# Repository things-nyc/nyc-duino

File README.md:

# nyc-duino

A simple demo board for the TTN NYC Hardware Office Hours!

## Soldering (optional)

Simple introduction to soldering by attaching the DHT11/22 and a 10k thru-hole pullup resistor. Male or female header can also be added to support Arduino shields.

## Arduino

### Installing

```
https://www.arduino.cc/en/Main/Software
```

### Libraries Needed

Sketch -> Include Library -> Manage Libraries

* Adafruit Unified Sensor - by Adafruit
* DHT sensor library - by Adafruit
* TheThingsNetwork - by The Things Network
* CayenneLPP - by The Things Network

## The Things Network

The Things Network is our LoRaWAN network server.

### Create Account

### Create Application

### Add Cayenne Integration

Also choose Cayenne LPP from Payload Formats tab.

### Add Device

Upload DeviceInfo sketch from TheThingsNetwork library to get DevEUI.

## Firmware

Download nycDuino-demo.ino from this repo.

Use the AppEUI and AppKey from TTN dashboard to personalize the Arduino sketch on lines 6 and 7.

Tools -> Board -> Arduino Leonardo

Upload.

## Cayenne

### Create Account

### Add Device

LoRa -> The Things Network -> Cayenne LPP

## Bonus Round

* Don't use delay() to time transmissions
* Use downlink to set onboard LED state
* Lower power by using sleep and idle

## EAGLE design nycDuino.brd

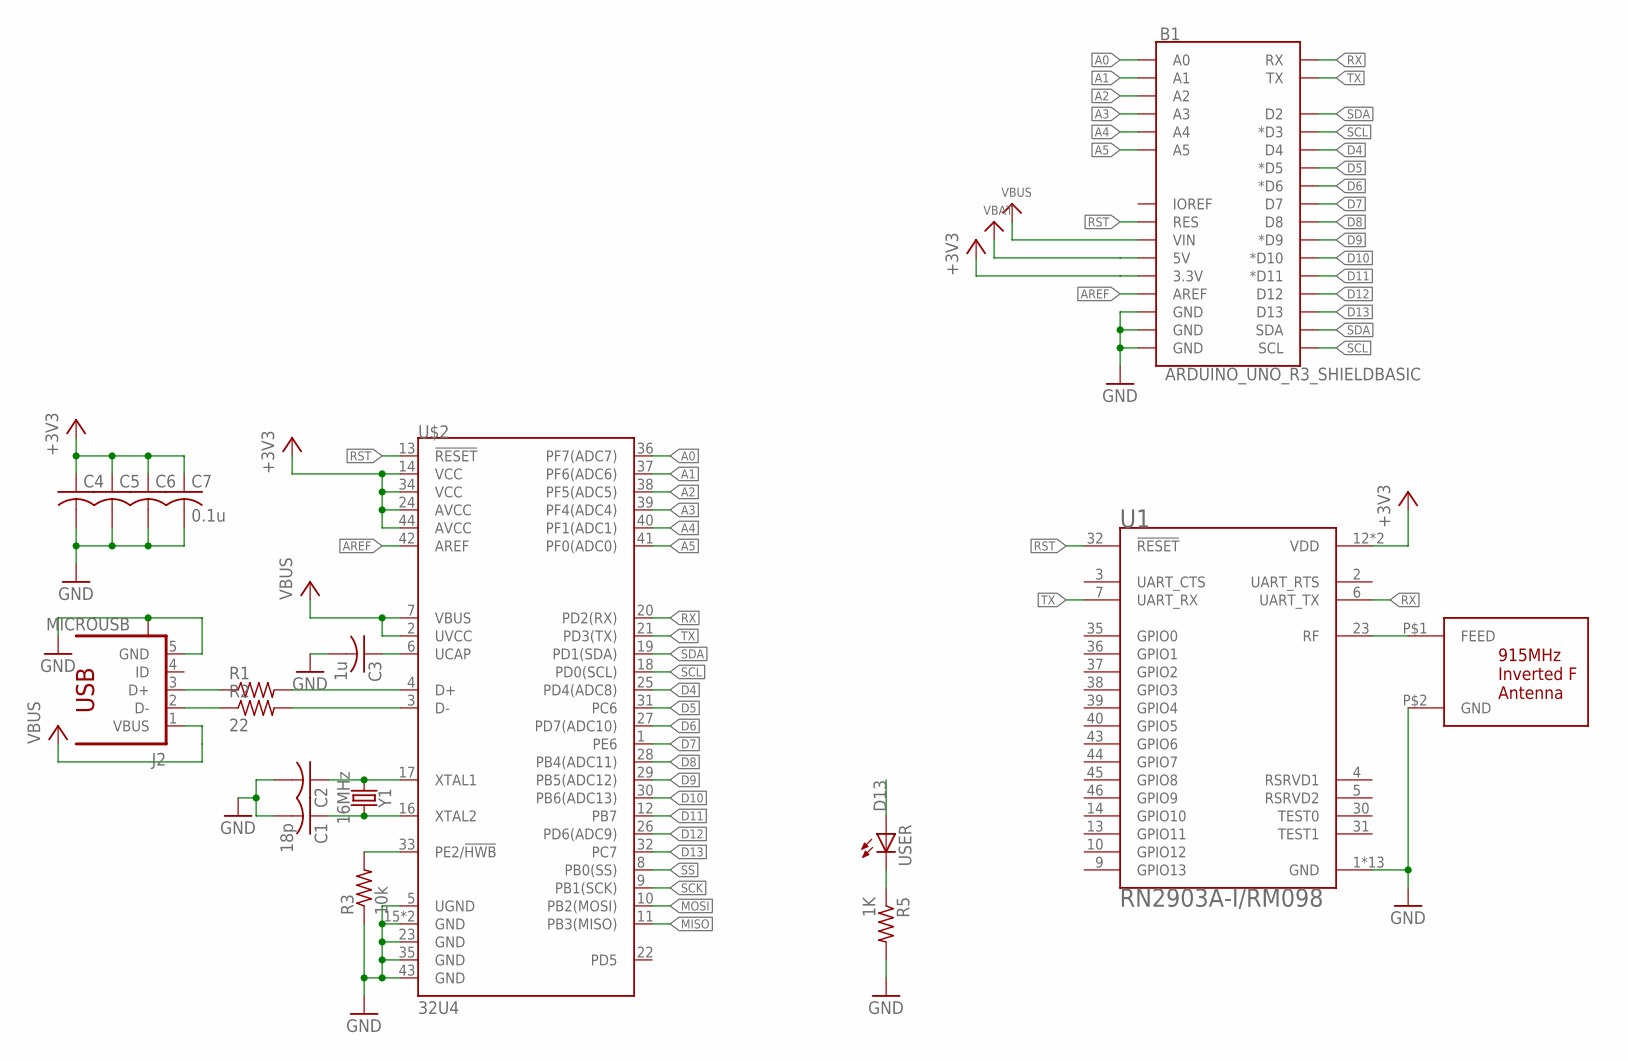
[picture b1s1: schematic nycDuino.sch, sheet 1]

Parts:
B1: ARDUINO_UNO_R3_SHIELDBASIC; UNO_R3_SHIELD
C1: 18p; C0603
C2, C4, C5, C6: C-USC0603; C0603
C3: 1u; C0603
C7: 0.1u; C0603
J2: MICROUSB; 10118192-0001LF
R1: R-US_R0603; R0603
R2: 22; R0603
R3: 10k; R0603
R5: 1K; R0603
U1: RN2903A-I/RM098; XCVR_RN2903A-I/RM098
U$1: 915MHZ; 915MHZ-F-NOMATCH
U$2: 32U4; QFN-44
USER: LEDCHIP-LED0603; CHIP-LED0603
Y1: 16MHz; CRYSTAL-SMD-5X3.2-4PAD

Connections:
+3V3: B1.3.3V, C4.1, C5.1, C6.1, C7.1, U1.12 (VDD), U1.34 (VDD), U$2.14 (VCC), U$2.24 (AVCC), U$2.34 (VCC), U$2.44 (AVCC); also elsewhere on the board
A0: B1.A0, U$2.36 (PF7(ADC7))
A1: B1.A1, U$2.37 (PF6(ADC6))
A2: B1.A2, U$2.38 (PF5(ADC5))
A3: B1.A3, U$2.39 (PF4(ADC4))
A4: B1.A4, U$2.40 (PF1(ADC1))
A5: B1.A5, U$2.41 (PF0(ADC0))
AREF: B1.AREF, U$2.42 (AREF); also elsewhere on the board
D4: B1.D4, U$2.25 (PD4(ADC8)); also elsewhere on the board
D5: B1.D5 (*D5), U$2.31 (PC6)
D6: B1.D6 (*D6), U$2.27 (PD7(ADC10))
D7: B1.D7, U$2.1 (PE6)
D8: B1.D8, U$2.28 (PB4(ADC11))
D9: B1.D9 (*D9), U$2.29 (PB5(ADC12))
D10: B1.D10 (*D10), U$2.30 (PB6(ADC13))
D11: B1.D11 (*D11), U$2.12 (PB7)
D12: B1.D12, U$2.26 (PD6(ADC9))
D13: B1.D13, U$2.32 (PC7), USER.A
GND: B1.GND@0 (GND), B1.GND@1 (GND), B1.GND@2 (GND), C1.2, C2.2, C3.2, C4.2, C5.2, C6.2, C7.2, J2.5 (GND), J2.M1 (S), J2.M2 (S), J2.S1 (S), J2.S2 (S), J2.S3 (S), J2.S4 (S), R3.1, R5.2, U1.1 (GND), U1.8 (GND), U1.11 (GND), U1.20 (GND), U1.21 (GND), U1.22 (GND), U1.24 (GND), U1.26 (GND), U1.27 (GND), U1.28 (GND), U1.33 (GND), U1.41 (GND), U1.47 (GND), U$1.P$2 (GND), U$2.5 (UGND), U$2.15 (GND), U$2.23 (GND), U$2.35 (GND), U$2.43 (GND), U$2.45 (GND); also elsewhere on the board
MISO: U$2.11 (PB3(MISO)); also elsewhere on the board
MOSI: U$2.10 (PB2(MOSI)); also elsewhere on the board
unnamed: U1.23 (RF), U$1.P$1 (FEED)
unnamed: J2.3 (D+), R1.1
unnamed: J2.2 (D-), R2.1
unnamed: R1.2, U$2.4 (D+)
unnamed: R2.2, U$2.3 (D-)
unnamed: C2.1, U$2.17 (XTAL1), Y1.1
unnamed: C1.1, U$2.16 (XTAL2), Y1.3 (2)
unnamed: C3.1, U$2.6 (UCAP)
unnamed: R3.2, U$2.33 (PE2/!HWB)
unnamed: R5.1, USER.C
RST: B1.RES, U1.32 (!RESET), U$2.13 (!RESET); also elsewhere on the board
RX: B1.RX, U1.6 (UART_TX), U$2.20 (PD2(RX))
SCK: U$2.9 (PB1(SCK)); also elsewhere on the board
SCL: B1.D3 (*D3), B1.SCL, U$2.18 (PD0(SCL))
SDA: B1.D2, B1.SDA, U$2.19 (PD1(SDA))
SS: U$2.8 (PB0(SS))
TX: B1.TX, U1.7 (UART_RX), U$2.21 (PD3(TX))
VBAT: B1.5V; also elsewhere on the board
VBUS: B1.VIN, J2.1 (VBUS), U$2.2 (UVCC), U$2.7 (VBUS); also elsewhere on the board

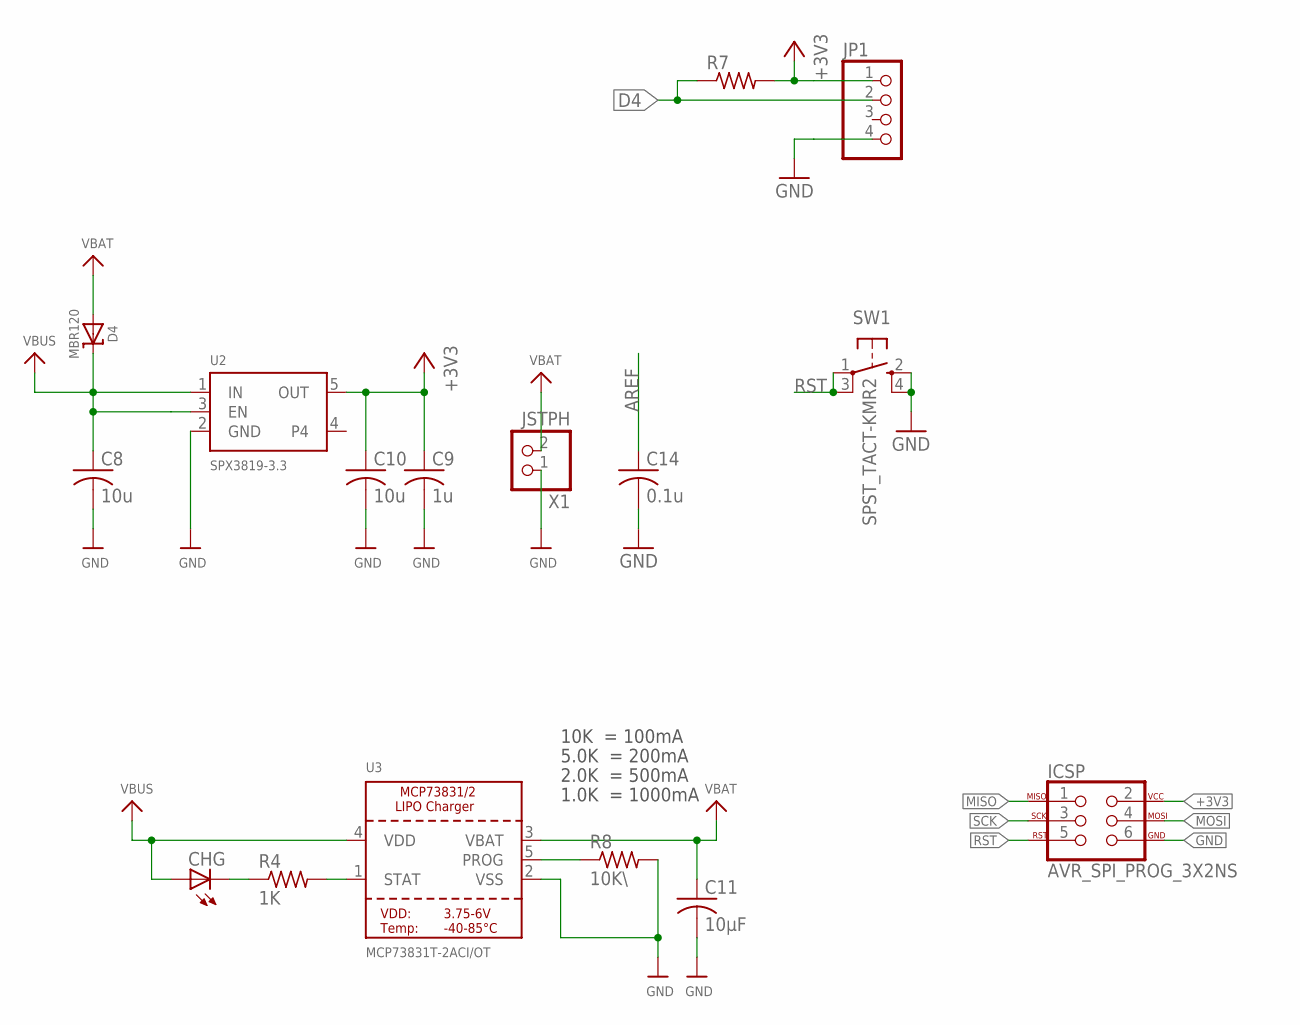
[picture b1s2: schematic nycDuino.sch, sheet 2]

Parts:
C8, C10: 10u; C0603
C9: 1u; C0603
C11: 10µF; C0603
C14: 0.1u; C0603
CHG: LEDCHIP-LED0603; CHIP-LED0603
D4: MBR120; SOD-123
ICSP: AVR_SPI_PROG_3X2NS; 2X3-NS
JP1: PINHD-1X4; 1X04
R4: 1K; R0603
R7: R-US_0207/7; 0207/7
R8: 10K\; R0603
SW1: SPST_TACT-KMR2; KMR2
U2: SPX3819-3.3; SOT23-5
U3: MCP73831T-2ACI/OT; SOT23-5
X1: JSTPH; JSTPH2

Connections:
+3V3: C9.1, C10.1, ICSP.2, JP1.1, R7.2, U2.5 (OUT); also elsewhere on the board
AREF: C14.1; also elsewhere on the board
D4: JP1.2, R7.1; also elsewhere on the board
GND: C8.2, C9.2, C10.2, C11.2, C14.2, ICSP.6, JP1.4, R8.2, SW1.2 (S), SW1.4 (S1), U2.2 (GND), U3.2 (VSS), X1.1; also elsewhere on the board
MISO: ICSP.1; also elsewhere on the board
MOSI: ICSP.4; also elsewhere on the board
unnamed: CHG.C, R4.1
unnamed: R4.2, U3.1 (STAT)
unnamed: R8.1, U3.5 (PROG)
RST: ICSP.5, SW1.1, SW1.3 (P1); also elsewhere on the board
SCK: ICSP.3; also elsewhere on the board
VBAT: C11.1, D4.A, U3.3 (VBAT), X1.2; also elsewhere on the board
VBUS: C8.1, CHG.A, D4.C, U2.1 (IN), U2.3 (EN), U3.4 (VDD); also elsewhere on the board

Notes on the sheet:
10K = 100mA
5.0K = 200mA
2.0K = 500mA
1.0K = 1000mA

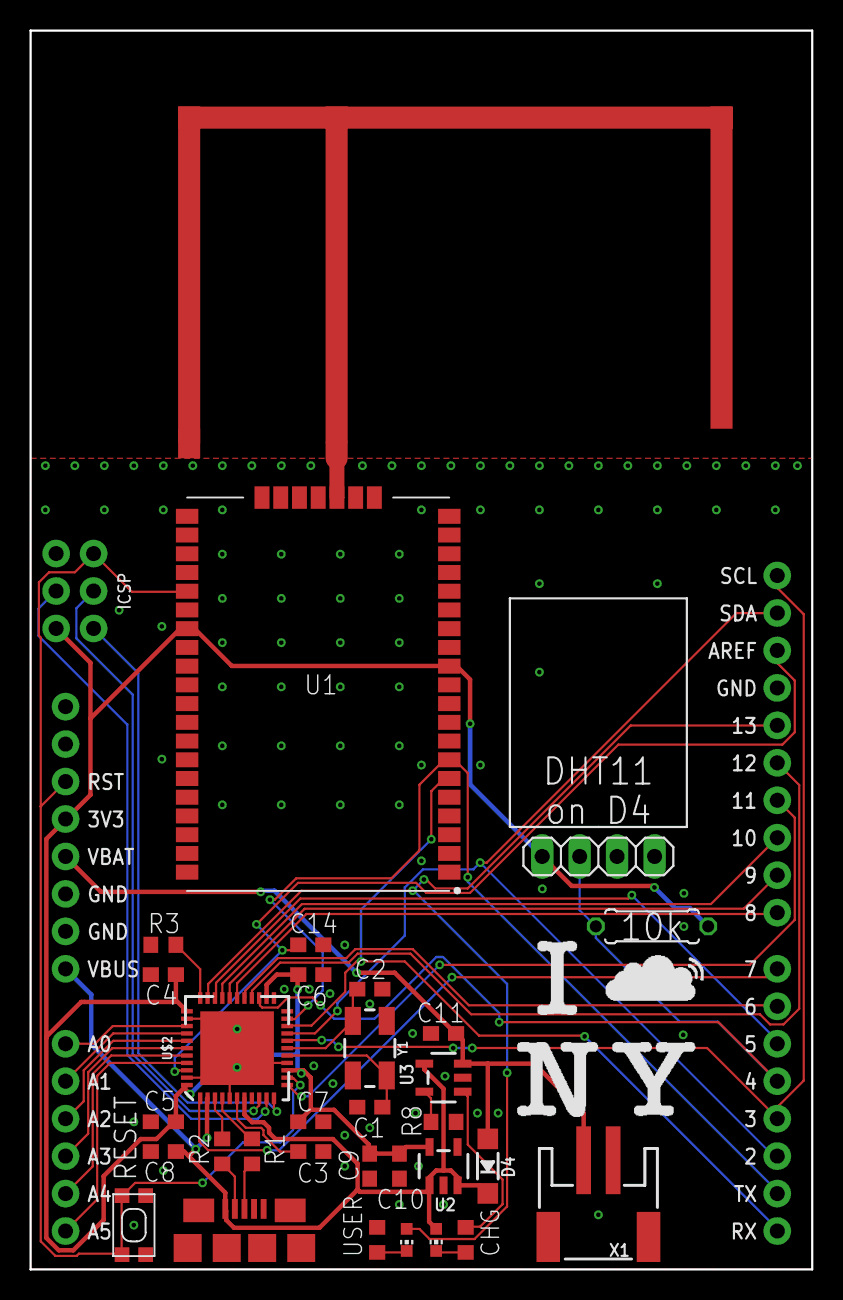
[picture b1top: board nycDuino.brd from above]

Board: 2 copper layers, 53.0 x 84.0 mm, 34 parts (0 on the bottom side), 42 nets.

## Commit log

2019-03-13 added vcc measurement

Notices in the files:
parts and their libraries:
SparkFun-Clocks: Licensing: Creative Commons ShareAlike 4.0 International - https://creativecommons.org/licenses/by-sa/4.0
microbuilder: This work is placed in the public domain, and may be freely used for commercial and non-commercial work with the following conditions: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
